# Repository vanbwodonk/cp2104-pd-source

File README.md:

# CP2104 USB Serial with PD source

This project is the result of research for 2 things, USB serial data for Android devices and being able to charge using a valid PD protocol. Common Type-C cables include two types: dual-head Type-C interface (full function) and Type-A to Type-C interface. The dual-head Type-C interface cable is too expensive and has limited usage scenarios, so Type-A to Type-C cable still has a large market. Type-A to Type-C cables are divided into two types: charging only and charging and data transmission. This project introduces a cable that can both charge and transmit serial data using the LDR6023SS USB PD communication chip from Lederer . It is simple in design and low in cost.

### Main functions of LDR6023:

1. Support USB PD 2.0, compatible with USB PD 3.0.
2. Support two USB-C DRP ports.
3. Support transparent transmission of PDO and REQUEST negotiation between the adapter and the smart device.
4. Automatically switch between DR_SWAP and UFP modes.

### Example simple schematic:

Since it is applied to wires, the chip package should be as small as possible. The smallest package of the LDR6023 series is SSOP-16, and the specific model is LDR6023SS. The schematic diagram is shown below:

### Link:

I found all this documentation from chinnese web. Please use google translate or somehing: 

1. https://www.sekorm.com/news/76945168.html

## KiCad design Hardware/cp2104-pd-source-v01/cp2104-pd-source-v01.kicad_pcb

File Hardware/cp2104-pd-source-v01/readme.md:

### Easyeda2kicad

Pull LDR6023C library from Easyeda with python library easyeda2kicad. Run terminal inside kicad project folder, then run this command

```bash
easyeda2kicad --lcsc_id C2919628 --full --overwrite --output ./easyeda2kicad/easyeda2kicad --project-relative
```

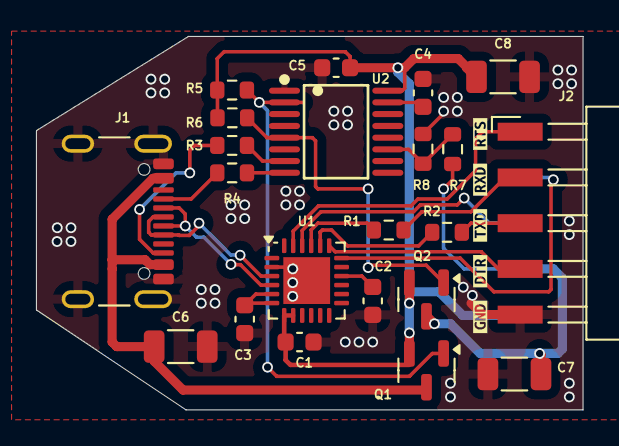
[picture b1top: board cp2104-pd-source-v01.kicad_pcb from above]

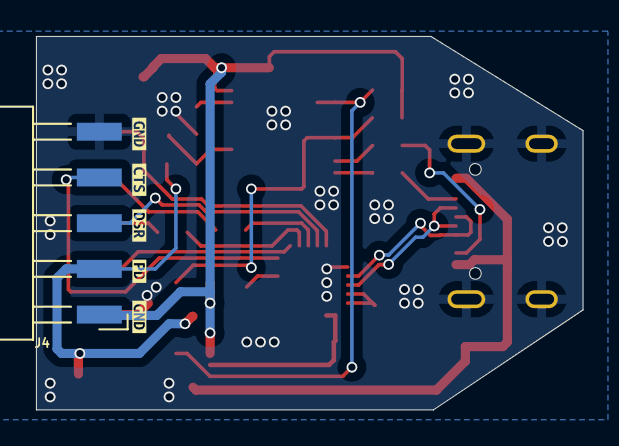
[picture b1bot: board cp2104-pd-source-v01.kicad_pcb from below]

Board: 2 copper layers, 30.4 x 20.7 mm, 33 parts (6 on the bottom side), 24 nets.

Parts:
C1, C3: 1uF; C_0603_1608Metric
C2: 4.7uF; C_0603_1608Metric
C4: 1nF; C_0603_1608Metric
C5: 100nF; C_0603_1608Metric
C6, C7, C8: 22uF; C_1206_3216Metric
J1: USB_C_Receptacle_USB2.0_16P; USB_C_Receptacle_GCT_USB4105-xx-A_16P_TopMnt_Horizontal
J2: HEADER TOP; Harwin_M20-89005xx_1x05_P2.54mm_Horizontal
J4: HEADER BOT; Harwin_M20-89005xx_1x05_P2.54mm_Horizontal
Q1, Q2: AO3400A; SOT-23
R1, R2: 470; R_0603_1608Metric
R3, R4: 100; R_0603_1608Metric
R5, R6: 10K; R_0603_1608Metric
R7: 36K; R_0603_1608Metric
R8: 12K; R_0603_1608Metric
U1: CP2104; QFN-24-1EP_4x4mm_P0.5mm_EP2.6x2.6mm
U2: LDR6023C; SSOP-16_L5.0-W4.4-P0.65-LS6.4-BL
kibuzzard-66B1E9B1: G***; kibuzzard-66B1E9B1
kibuzzard-66B1E9B7: G***; kibuzzard-66B1E9B7
kibuzzard-66B1E9BE: G***; kibuzzard-66B1E9BE
kibuzzard-66B1E90B: G***; kibuzzard-66B1E90B
kibuzzard-66B1E91A: G***; kibuzzard-66B1E91A
kibuzzard-66B1E901: G***; kibuzzard-66B1E901
kibuzzard-66B1E950, kibuzzard-66B1E950#2: G***; kibuzzard-66B1E950
kibuzzard-66B1E959: G***; kibuzzard-66B1E959
kibuzzard-66B1E998: G***; kibuzzard-66B1E998

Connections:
+5V: C1.1, C5.1, C8.1, J4.1, Q1.2 (S), Q2.2 (S), R5.1, R6.1, U1.7 (REGIN), U1.8 (VBUS), U2.16 (VDD)
+5V_IN: C7.1, J4.2, Q2.3 (D), R7.1
C1_VBUS_DET: R7.2, R8.1, U2.11 (C1DT)
CC1: J1.A5 (CC1), R4.2
CC2: J1.B5 (CC2), R3.2
CTS: J4.4, U1.18 (~CTS)
D+: J1.A6 (D+), J1.B6 (D+), U1.3 (D+)
D-: J1.A7 (D-), J1.B7 (D-), U1.4 (D-)
DSR: J4.3, U1.22 (~DSR)
DTR: J2.4, U1.19 (~RTS)
GND: C1.2, C2.2, C3.2, C4.2, C5.2, C6.2, C7.2, C8.2, J1.A1 (GND), J1.A12 (GND), J1.B1 (GND), J1.B12 (GND), J1.S1 (SHIELD), J2.5, J4.5, R8.2, U1.2 (GND), U1.25 (GND), U2.1 (VSS)
unnamed: R2.2, U1.20 (RXD)
unnamed: R1.2, U1.21 (TXD)
unnamed: C3.1, U1.5 (VIO), U1.6 (VDD)
unnamed: C2.1, U1.16 (VPP)
unnamed: R4.1, U2.8 (C0CC1)
unnamed: R3.1, U2.7 (C0CC2)
unnamed: C4.1, U2.15 (PDLDO)
RTS: J2.1, U1.23 (~DTR)
RXD0: J2.2, R1.1
TXD0: J2.3, R2.1
VADP_EN: Q2.1 (G), R6.2, U2.5 (VadpEN)
VBUS: C6.1, J1.A4 (VBUS), J1.A9 (VBUS), J1.B4 (VBUS), J1.B9 (VBUS), Q1.3 (D)
VBUS_EN: Q1.1 (G), R5.2, U2.2 (VBEN)

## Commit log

2024-07-31 update readme.
2024-07-31 fix readme
2024-08-01 add gitignore
2024-08-01 try easyeda2kicad to local lib
2024-08-06 add final pcb
2024-08-06 ignore .lck files
2024-08-06 add jlcpcb production files
2024-08-06 exclude some component from bom
